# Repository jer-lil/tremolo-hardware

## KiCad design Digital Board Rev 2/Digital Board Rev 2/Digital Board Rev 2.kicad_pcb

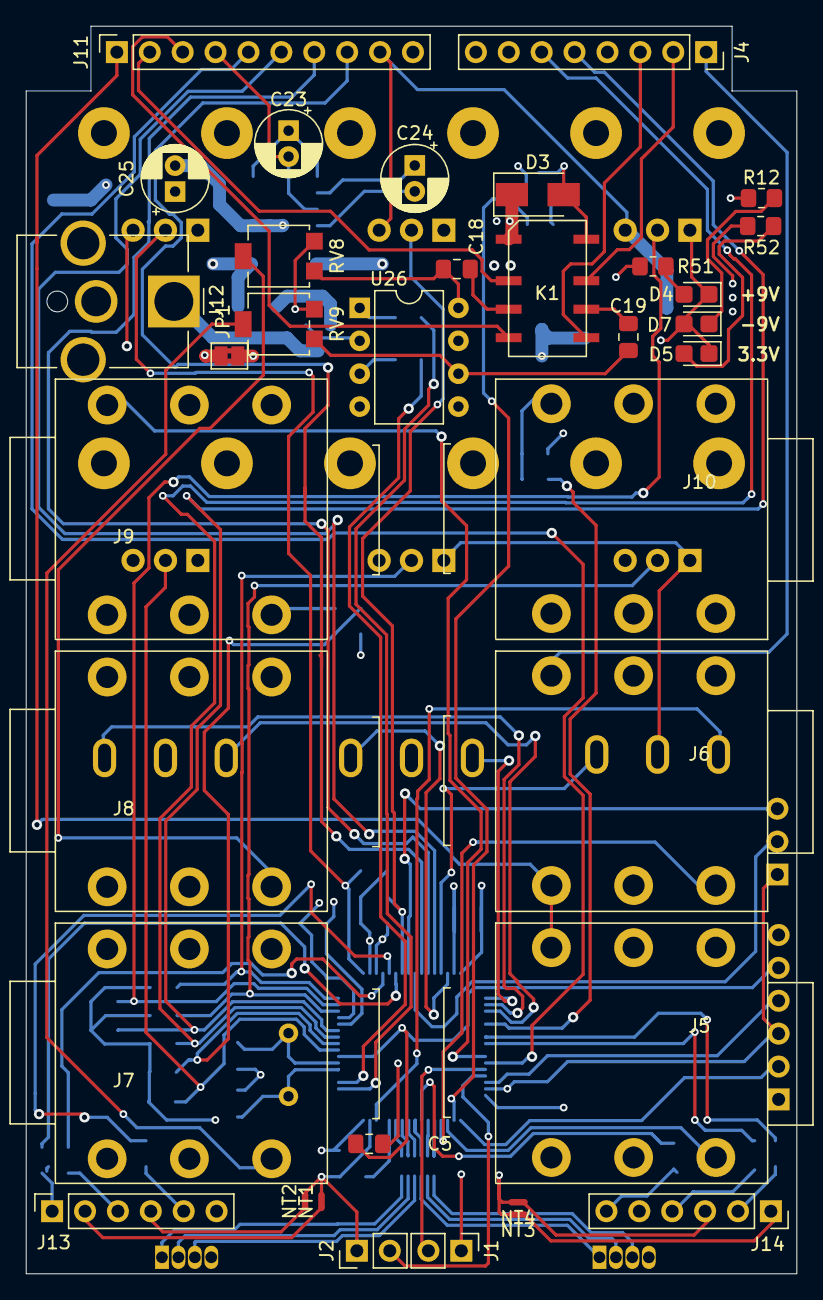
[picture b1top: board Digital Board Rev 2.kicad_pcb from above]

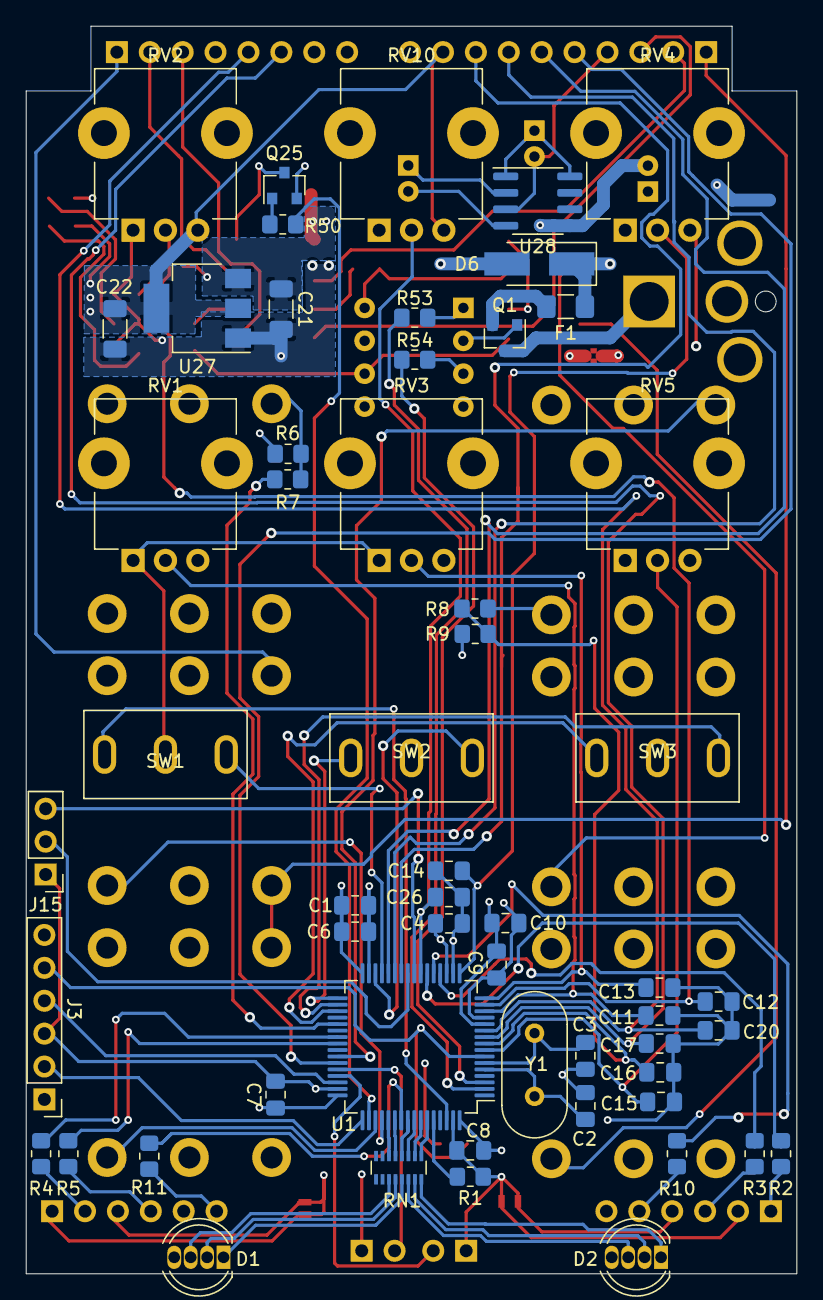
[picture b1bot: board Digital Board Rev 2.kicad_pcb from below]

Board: 4 copper layers, 59.5 x 96.3 mm, 91 parts (56 on the bottom side), 94 nets.

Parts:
C1: 4.7u; C_0805_2012Metric_Pad1.18x1.45mm_HandSolder
C2, C3: 18p; C_0805_2012Metric_Pad1.18x1.45mm_HandSolder
C4, C5, C6, C7, C8, C16, C17, C20: 100n; C_0805_2012Metric_Pad1.18x1.45mm_HandSolder
C9: 10n; C_0805_2012Metric_Pad1.18x1.45mm_HandSolder
C10: 1u; C_0805_2012Metric_Pad1.18x1.45mm_HandSolder
C11, C12, C13, C14, C15, C26: 100nF; C_0805_2012Metric_Pad1.18x1.45mm_HandSolder
C18, C19: 470n; C_0805_2012Metric_Pad1.18x1.45mm_HandSolder
C21, C22: 10u; C_1206_3216Metric_Pad1.33x1.80mm_HandSolder
C23, C24, C25: 100uF; CP_Radial_D5.0mm_P2.00mm
D1, D2: LED_RGBA; LED_D5.0mm-4_RGB
D3: B120-E3; D_SMA
D4, D5, D7: LED_Small; LED_0805_2012Metric_Castellated
D6: D_Zener; D_SMA_Handsoldering
F1: Polyfuse; Fuse_1206_3216Metric_Pad1.42x1.75mm_HandSolder
J1, J2: Conn_01x02_Male; PinHeader_1x02_P2.54mm_Vertical
J3: Conn_01x06_Male; PinHeader_1x06_P2.54mm_Vertical
J4: Conn_01x08_Female; PinSocket_1x08_P2.54mm_Vertical
J5, J6, J7, J8, J9, J10: AudioJack3_Switch; Jack_0.25in_TRS_Switched
J11: Conn_01x10_Female; PinSocket_1x10_P2.54mm_Vertical
J12: Barrel_Jack; BarrelJack_CUI_PJ-063AH_Horizontal_CircularHoles
J13, J14: Conn_01x06_Female; PinSocket_1x06_P2.54mm_Vertical
J15: Conn_01x03_Male; PinHeader_1x03_P2.54mm_Vertical
JP1: Jumper; SolderJumper-2_P1.3mm_Bridged2Bar_Pad1.0x1.5mm
K1: IM05; Relay_DPDT_NL_TE_IM05GR
NT1, NT2, NT3, NT4: Net-Tie_2; NetTie-2_SMD_Pad0.5mm
Q1: BSS83P; SOT-23
Q25: MMBT3904; SOT-23
R1, R8: 10k; R_0805_2012Metric_Pad1.20x1.40mm_HandSolder
R2, R3, R4, R5, R10, R11: 330; R_0805_2012Metric_Pad1.20x1.40mm_HandSolder
R6, R7, R12, R51: 1k; R_0805_2012Metric_Pad1.20x1.40mm_HandSolder
R9: 19.1k; R_0805_2012Metric_Pad1.20x1.40mm_HandSolder
R50: 2.2k; R_0805_2012Metric_Pad1.20x1.40mm_HandSolder
R52: 470; R_0805_2012Metric_Pad1.20x1.40mm_HandSolder
R53, R54: 630; R_0805_2012Metric_Pad1.20x1.40mm_HandSolder
RN1: R_Pack08; R_Array_Convex_8x0602
RV1, RV2, RV3, RV4, RV5, RV10: R_POT_TRIM; Potentiometer_9MM
RV8, RV9: 100k; Potentiometer_Bourns_3314G_Vertical
SW1, SW2, SW3: SW_SPDT_MSM; SW_Toggle_SPDT
U1: STM32F303R6Tx; LQFP-64_10x10mm_P0.5mm
U26: TLP222A-2; DIP-8_W7.62mm
U27: NCP1117-3.3_SOT223; SOT-223-3_TabPin2
U28: TC7662Bx0A; SOIC-8_3.9x4.9mm_P1.27mm
Y1: 8MHz; Crystal_HC49-U_Vertical

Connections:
+3V3: C1.1, C4.1, C6.1, C7.1, C8.1, C9.1, C10.1, C22.1, D1.4, D2.4, J3.1, J9.R, J11.9, R6.2, R52.1, RV1.3, RV2.3, RV3.3, RV4.3, RV5.3, RV10.3, U1.13, U1.19, U1.32, U1.48, U1.64, U27.2
+9V: C21.1, C23.1, D3.1, D6.1, F1.1, J4.7, K1.1, R51.1, U27.3, U28.1, U28.8
-9V: C25.2, J4.4, R12.2, U28.5
/Audio Jacks/CH1_OUT: J8.T, RV8.2
/Audio Jacks/CH1_OUT_PRE: C18.1, RV8.1, U26.8
/Audio Jacks/CH2_OUT: J7.T, RV9.2
/Audio Jacks/CH2_OUT_PRE: C19.1, RV9.1, U26.6
/BYP: J1.2, U1.44
/CH1_BYP: J11.2, K1.2
/CH1_EFF: J11.3, K1.4
/CH1_IN: J5.T, J6.TN, J11.1
/CH1_SW: J5.SN, U1.51
/CH2_BYP: J4.2, K1.7
/CH2_EFF: J4.3, K1.5
/CH2_IN: J4.1, J6.T
/CH2_SW: J6.SN, U1.52
/DEPTH: C12.1, RV2.2, U1.15
/DIP1: J11.8, U1.26
/DIP2: J11.7, U1.27
/DIP3: J11.6, U1.28
/DIP4: J11.5, U1.43
/ENV_MODE_1: SW3.3, U1.34
/ENV_MODE_2: SW3.1, U1.35
/EXP: C16.1, R8.2, R9.1, U1.9
/EXP_SW: J9.SN, U1.42
/HARM_MODE_1: SW1.3, U1.62
/HARM_MODE_2: SW1.1, U1.29
/LED1_B: RN1.6, U1.53
/LED1_G: RN1.5, U1.54
/LED1_R: RN1.4, U1.56
/LED2_B: RN1.3, U1.57
/LED2_G: RN1.2, U1.58
/LED2_R: RN1.1, U1.59
/LEDs/B1_R: D1.3, RN1.11
/LEDs/B2_R: D2.3, RN1.14
/LEDs/G1_R: D1.2, RN1.12
/LEDs/G2_R: D2.2, RN1.15
/LEDs/R1_R: D1.1, RN1.13
/LEDs/R2_R: D2.1, RN1.16
/MUTE1: R53.2, U1.2
/MUTE2: R54.2, U1.3
/NRST: C5.1, J3.5, U1.7
/OFFSET: C14.1, RV4.2, U1.17
/OSC1: C2.2, U1.5, Y1.2
/OSC2: C3.2, U1.6, Y1.1
/PAN_MODE_1: SW2.3, U1.30
/PAN_MODE_2: SW2.1, U1.33
/PWM1: R2.1, U1.22
/PWM2: R3.1, U1.20
/PWM3: R4.1, U1.39
/PWM4: R5.1, U1.40
/PWM_OUT_1: J13.1, R2.2
/PWM_OUT_2: J13.3, R3.2
/PWM_OUT_3: J14.2, R4.2
/PWM_OUT_4: J14.4, R5.2
/PWM_OUT_VOL_1: J13.5, R10.2
/PWM_OUT_VOL_2: J14.6, R11.2
/PWM_RTN_1: J13.2, NT1.1
/PWM_RTN_2: J13.4, NT2.1
/PWM_RTN_3: J14.1, NT3.1
/PWM_RTN_4: J14.3, NT4.1
/PWM_VOL_1: R10.1, U1.21
/PWM_VOL_2: R11.1, U1.55
/RATE: C11.1, RV1.2, U1.14
/RLY_SET: R50.2, U1.50
/SHAPE: C13.1, RV3.2, U1.16
/SUBDIV: C15.1, RV5.2, U1.8
/SWCLK: J3.2, U1.49
/SWDIO: J3.4, U1.46
/TAP: J2.2, U1.45
/TAP_EXT: R7.2, U1.37
/TRIM1: C17.1, J4.6, U1.10
/TRIM2: C20.1, J4.5, U1.11
/UART_RX: J15.2, U1.25
/UART_TX: J15.3, U1.24
/VOL: C26.1, RV10.2, U1.23
GNDA: J4.8, J5.S, J6.S, J7.S, J8.S, J11.10, JP1.2, RV8.3, RV9.3, U26.5, U26.7
GNDD: C1.2, C2.1, C3.1, C4.2, C5.2, C6.2, C7.2, C8.2, C9.2, C10.2, C11.2, C12.2, C13.2, C14.2, C15.2, C16.2, C17.2, C20.2, C21.2, C22.2, C23.2, C25.1, C26.2, D4.1, D5.1, D6.2, D7.2, J1.1, J2.1, J3.3, J9.S, J11.4, J12.2, J15.1, JP1.1, NT1.2, NT2.2, NT3.2, NT4.2, Q1.1, Q25.2, R1.1, R9.2, RV1.1, RV2.1, RV3.1, RV4.1, RV5.1, RV10.1, SW1.2, SW2.2, SW3.2, U1.12, U1.18, U1.31, U1.47, U1.63, U26.2, U26.4, U27.1, U28.3
unnamed: C18.2, K1.3
unnamed: C19.2, K1.6
unnamed: C24.1, U28.2
unnamed: C24.2, U28.4
unnamed: D3.2, K1.8, Q25.3
unnamed: D4.2, R51.2
unnamed: D5.2, R52.2
unnamed: D7.1, R12.1
unnamed: F1.2, Q1.2
unnamed: J9.T, R8.1
unnamed: J10.T, R6.1, R7.1
unnamed: J12.1, Q1.3
unnamed: Q25.1, R50.1
unnamed: R1.2, U1.60
unnamed: R53.1, U26.1
unnamed: R54.1, U26.3
